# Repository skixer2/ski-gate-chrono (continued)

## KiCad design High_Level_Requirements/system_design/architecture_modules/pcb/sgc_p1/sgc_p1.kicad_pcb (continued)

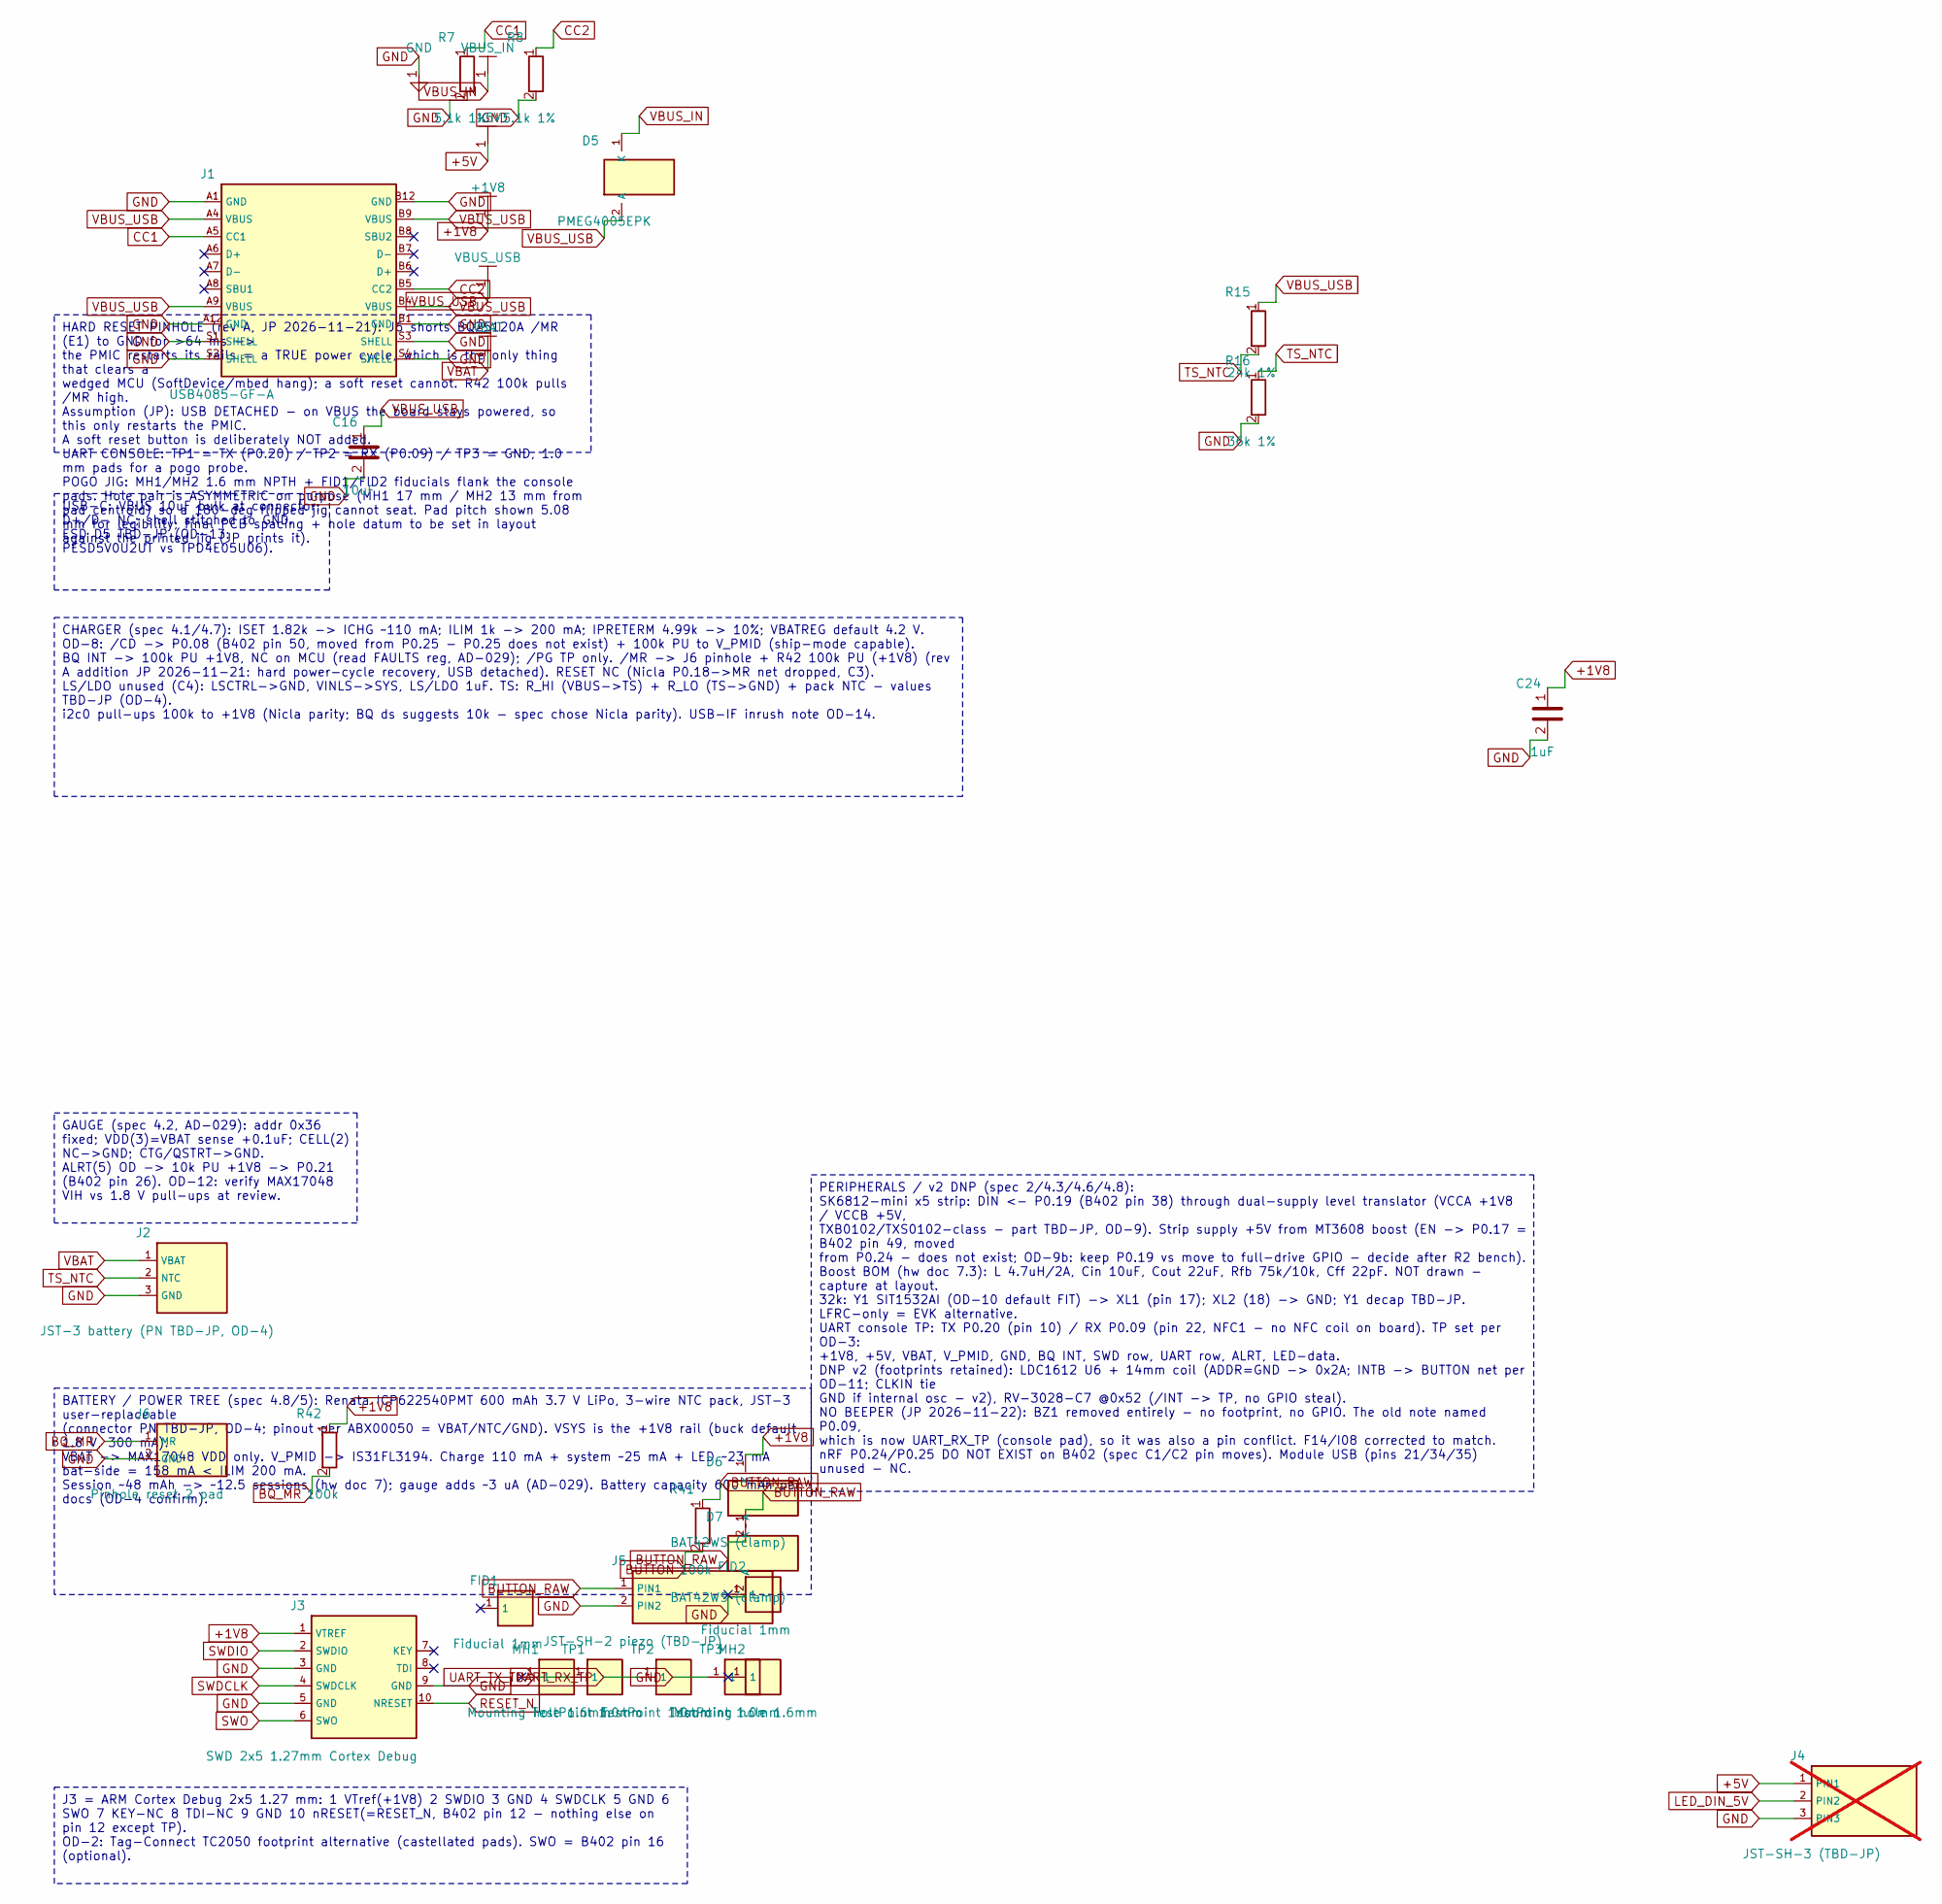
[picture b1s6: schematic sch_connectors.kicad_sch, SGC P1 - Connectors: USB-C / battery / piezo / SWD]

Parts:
C16: 10uF; C_0603_1608Metric
C24: 1uF; C_0402_1005Metric
D5: PMEG4005EPK; D_SOD-1608_DFN1608D-2
D6, D7: BAT42WS (clamp); D_SOD-323
FID1, FID2: Fiducial 1mm; Fiducial_1mm_Mask2mm
J1: USB4085-GF-A; USB_C_Receptacle_GCT_USB4085
J2: JST-3 battery (PN TBD-JP, OD-4); JST_ACH_BM03B-ACHSS-GAN-ETF_1x03-1MP_P1.20mm_Vertical
J3: SWD 2x5 1.27mm Cortex Debug; PinHeader_2x05_P1.27mm_Vertical
J4: JST-SH-3 (TBD-JP); JST_SH_SM03B-SRSS-TB_1x03-1MP_P1.00mm_Horizontal; not fitted
J5: JST-SH-2 piezo (TBD-JP); JST_SH_SM02B-SRSS-TB_1x02-1MP_P1.00mm_Horizontal
J6: Pinhole reset 2 pad; PINHOLE-2
MH1, MH2: Mounting hole 1.6mm; MountingHole_1.6mm
R7, R8: 5.1k 1%; R_0402_1005Metric
R15: 24k 1%; R_0402_1005Metric
R16: 36k 1%; R_0402_1005Metric
R41, R42: 100k; R_0402_1005Metric
TP1, TP2, TP3: TestPoint 1.0mm; TestPoint_Pad_D1.0mm

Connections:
+1V8: C24.1, D6.1 (K), J3.1 (VTREF), R42.1; also elsewhere on the board
+5V: J4.1 (PIN1); also elsewhere on the board
BQ_MR: J6.1 (MR), R42.2; also elsewhere on the board
BUTTON: R41.2; also elsewhere on the board
BUTTON_RAW: D6.2 (A), D7.1 (K), J5.1 (PIN1), R41.1
CC1: J1.A5 (CC1), R7.1
CC2: J1.B5 (CC2), R8.1
GND: C16.2, C24.2, D7.2 (A), J1.A1 (GND), J1.A12 (GND), J1.B1 (GND), J1.B12 (GND), J1.S1 (SHELL), J1.S2 (SHELL), J1.S3 (SHELL), J1.S4 (SHELL), J1.SH, J2.3 (GND), J3.3 (GND), J3.5 (GND), J3.9 (GND), J4.3 (PIN3), J5.2 (PIN2), J6.2 (GND), R7.2, R8.2, R16.2, TP3.1; also elsewhere on the board
LED_DIN_5V: J4.2 (PIN2); also elsewhere on the board
RESET_N: J3.10 (NRESET); also elsewhere on the board
SWDCLK: J3.4 (SWDCLK); also elsewhere on the board
SWDIO: J3.2 (SWDIO); also elsewhere on the board
SWO: J3.6 (SWO); also elsewhere on the board
TS_NTC: J2.2 (NTC), R15.2, R16.1; also elsewhere on the board
UART_RX_TP: TP2.1; also elsewhere on the board
UART_TX_TP: TP1.1; also elsewhere on the board
VBAT: J2.1 (VBAT); also elsewhere on the board
VBUS_IN: D5.1 (K); also elsewhere on the board
VBUS_USB: C16.1, D5.2 (A), J1.A4 (VBUS), J1.A9 (VBUS), J1.B4 (VBUS), J1.B9 (VBUS), R15.1

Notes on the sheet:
CHARGER (spec 4.1/4.7): ISET 1.82k -> ICHG ~110 mA; ILIM 1k -> 200 mA; IPRETERM 4.99k -> 10%; VBATREG default 4.2 V. OD-8: /CD -> P0.08 (B402 pin 50, moved from P0.25 - P0.25 does not exist) + 100k PU to V_PMID (ship-mode capable). BQ INT -> 100k PU +1V8, NC on MCU (read FAULTS reg, AD-029); /PG TP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
HARD RESET PINHOLE (rev A, JP 2026-11-21): J6 shorts BQ25120A /MR (E1) to GND for >64 ms -> the PMIC restarts its rails = a TRUE power cycle, which is the only thing that clears a wedged MCU (SoftDevice/mbed hang); a soft reset cannot. R42 100k pulls /MR high. Assumption (JP): USB DETACHED - on VBU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
USB-C: VBUS 10uF bulk at connector; D+/D- NC; shell stitched to GND. ESD D5 TBD-JP (OD-13: PESD5V0U2UT vs TPD4E05U06).
GAUGE (spec 4.2, AD-029): addr 0x36 fixed; VDD(3)=VBAT sense +0.1uF; CELL(2) NC->GND; CTG/QSTRT->GND. ALRT(5) OD -> 10k PU +1V8 -> P0.21 (B402 pin 26). OD-12: verify MAX17048 VIH vs 1.8 V pull-ups at review.
PERIPHERALS / v2 DNP (spec 2/4.3/4.6/4.8): SK6812-mini x5 strip: DIN <- P0.19 (B402 pin 38) through dual-supply level translator (VCCA +1V8 / VCCB +5V, TXB0102/TXS0102-class - part TBD-JP, OD-9). Strip supply +5V from MT3608 boost (EN -> P0.17 = B402 pin 49, moved from P0.24 - does not exist; OD-9b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
BATTERY / POWER TREE (spec 4.8/5): Renata ICP622540PMT 600 mAh 3.7 V LiPo, 3-wire NTC pack, JST-3 user-replaceable (connector PN TBD-JP, OD-4; pinout per ABX00050 = VBAT/NTC/GND). VSYS is the +1V8 rail (buck default 1.8 V, 300 mA). VBAT -> MAX17048 VDD only. V_PMID -> IS31FL3194. Charge 110 mA + sy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
J3 = ARM Cortex Debug 2x5 1.27 mm: 1 VTref(+1V8) 2 SWDIO 3 GND 4 SWDCLK 5 GND 6 SWO 7 KEY-NC 8 TDI-NC 9 GND 10 nRESET(=RESET_N, B402 pin 12 - nothing else on pin 12 except TP). OD-2: Tag-Connect TC2050 footprint alternative (castellated pads). SWO = B402 pin 16 (optional).

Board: 4 copper layers, 79 parts (0 on the bottom side), 65 nets, no tracks yet.
